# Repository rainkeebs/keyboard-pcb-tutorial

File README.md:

# keyboard-pcb-tutorial
 just tryna learn kicad lol

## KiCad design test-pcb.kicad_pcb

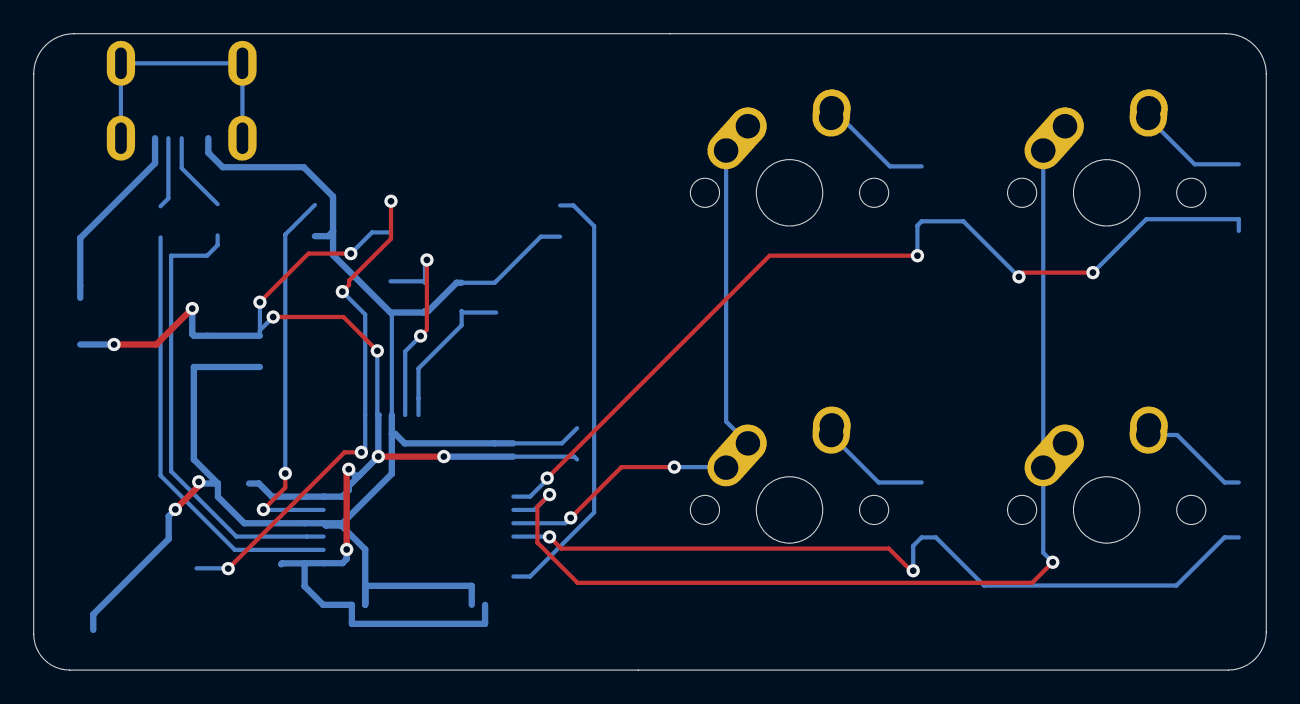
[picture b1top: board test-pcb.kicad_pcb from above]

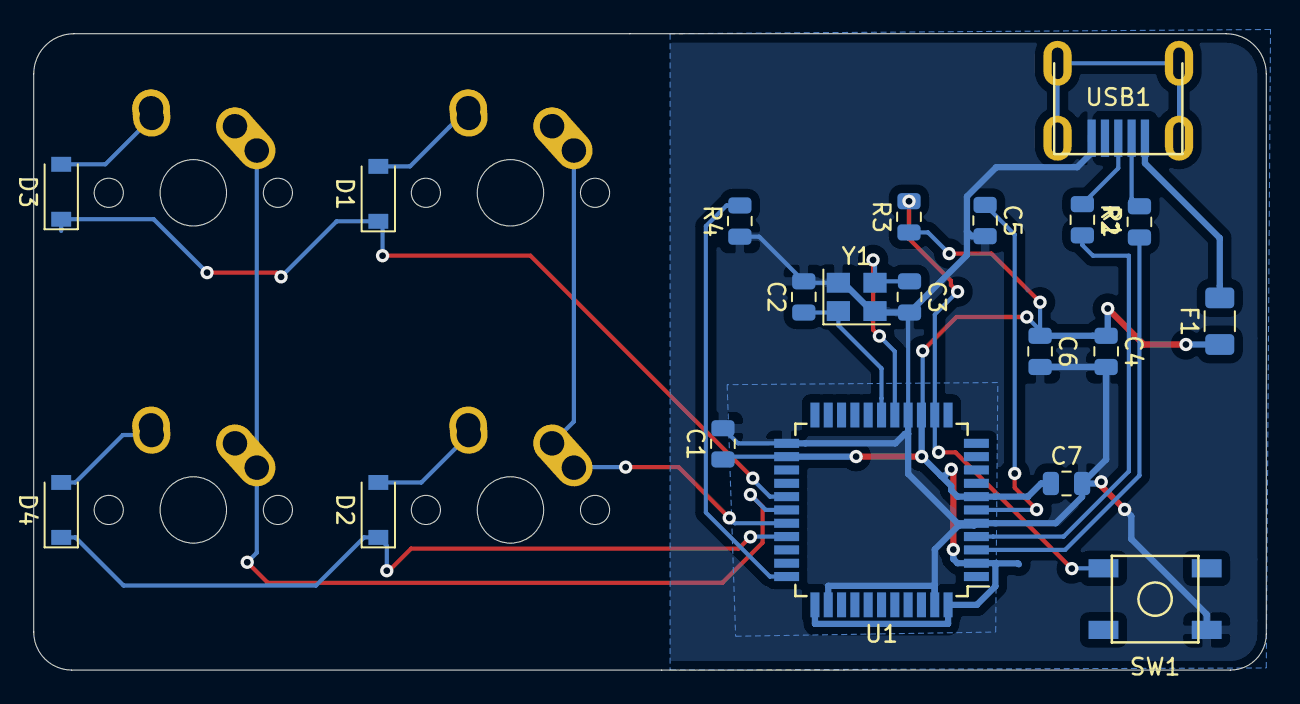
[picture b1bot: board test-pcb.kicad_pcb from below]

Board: 2 copper layers, 74.0 x 38.2 mm, 24 parts (20 on the bottom side), 20 nets.

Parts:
C1, C4, C7: 0.1uF; C_0805_2012Metric
C2, C3: 22pF; C_0805_2012Metric
C5: 1uF; C_0805_2012Metric
C6: 10uF; C_0805_2012Metric
D1, D2, D3, D4: D_Small; D_SOD-123
F1: 500mA; Fuse_1206_3216Metric
MX1, MX2, MX3, MX4: MX-NoLED; MX-1U-NoLED
R1, R2: 22; R_0805_2012Metric
R3, R4: 10k; R_0805_2012Metric
SW1: SW_Push; SKQG-1155865
U1: ATmega32U4-AU; TQFP-44_10x10mm_P0.8mm
USB1: Molex-0548190589
Y1: 16MHz; Crystal_SMD_3225-4Pin_3.2x2.5mm

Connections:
+5V: C1.1, C4.1, C6.1, C7.1, F1.1, R3.1, U1.2, U1.7, U1.14, U1.24, U1.34, U1.44
COL0: MX1.1, MX2.1, U1.29
COL1: MX3.1, MX4.1, U1.28
D+: R2.1, USB1.3
D-: R1.2, USB1.4
GND: C1.2, C2.2, C3.2, C4.2, C5.2, C6.2, C7.2, R4.1, SW1.1, U1.5, U1.15, U1.23, U1.35, U1.43, USB1.1, Y1.2, Y1.4
unnamed: C2.1, U1.17, Y1.1
unnamed: C3.1, U1.16, Y1.3
unnamed: C5.1, U1.6
unnamed: D1.2, MX1.2
unnamed: D2.2, MX2.2
unnamed: D3.2, MX3.2
unnamed: D4.2, MX4.2
unnamed: R1.1, U1.3
unnamed: R2.2, U1.4
unnamed: R3.2, SW1.2, U1.13
unnamed: R4.2, U1.33
ROW0: D1.1, D3.1, U1.27
ROW1: D2.1, D4.1, U1.30
VCC: F1.2, USB1.5

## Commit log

2020-10-19 initialize project
2020-10-19 add submodules
2020-10-19 add footprint libraries
2020-10-19 bruh
2020-10-19 adding another library cuz kicad sucks
2020-10-19 added footprints
2020-10-19 gerbers!
